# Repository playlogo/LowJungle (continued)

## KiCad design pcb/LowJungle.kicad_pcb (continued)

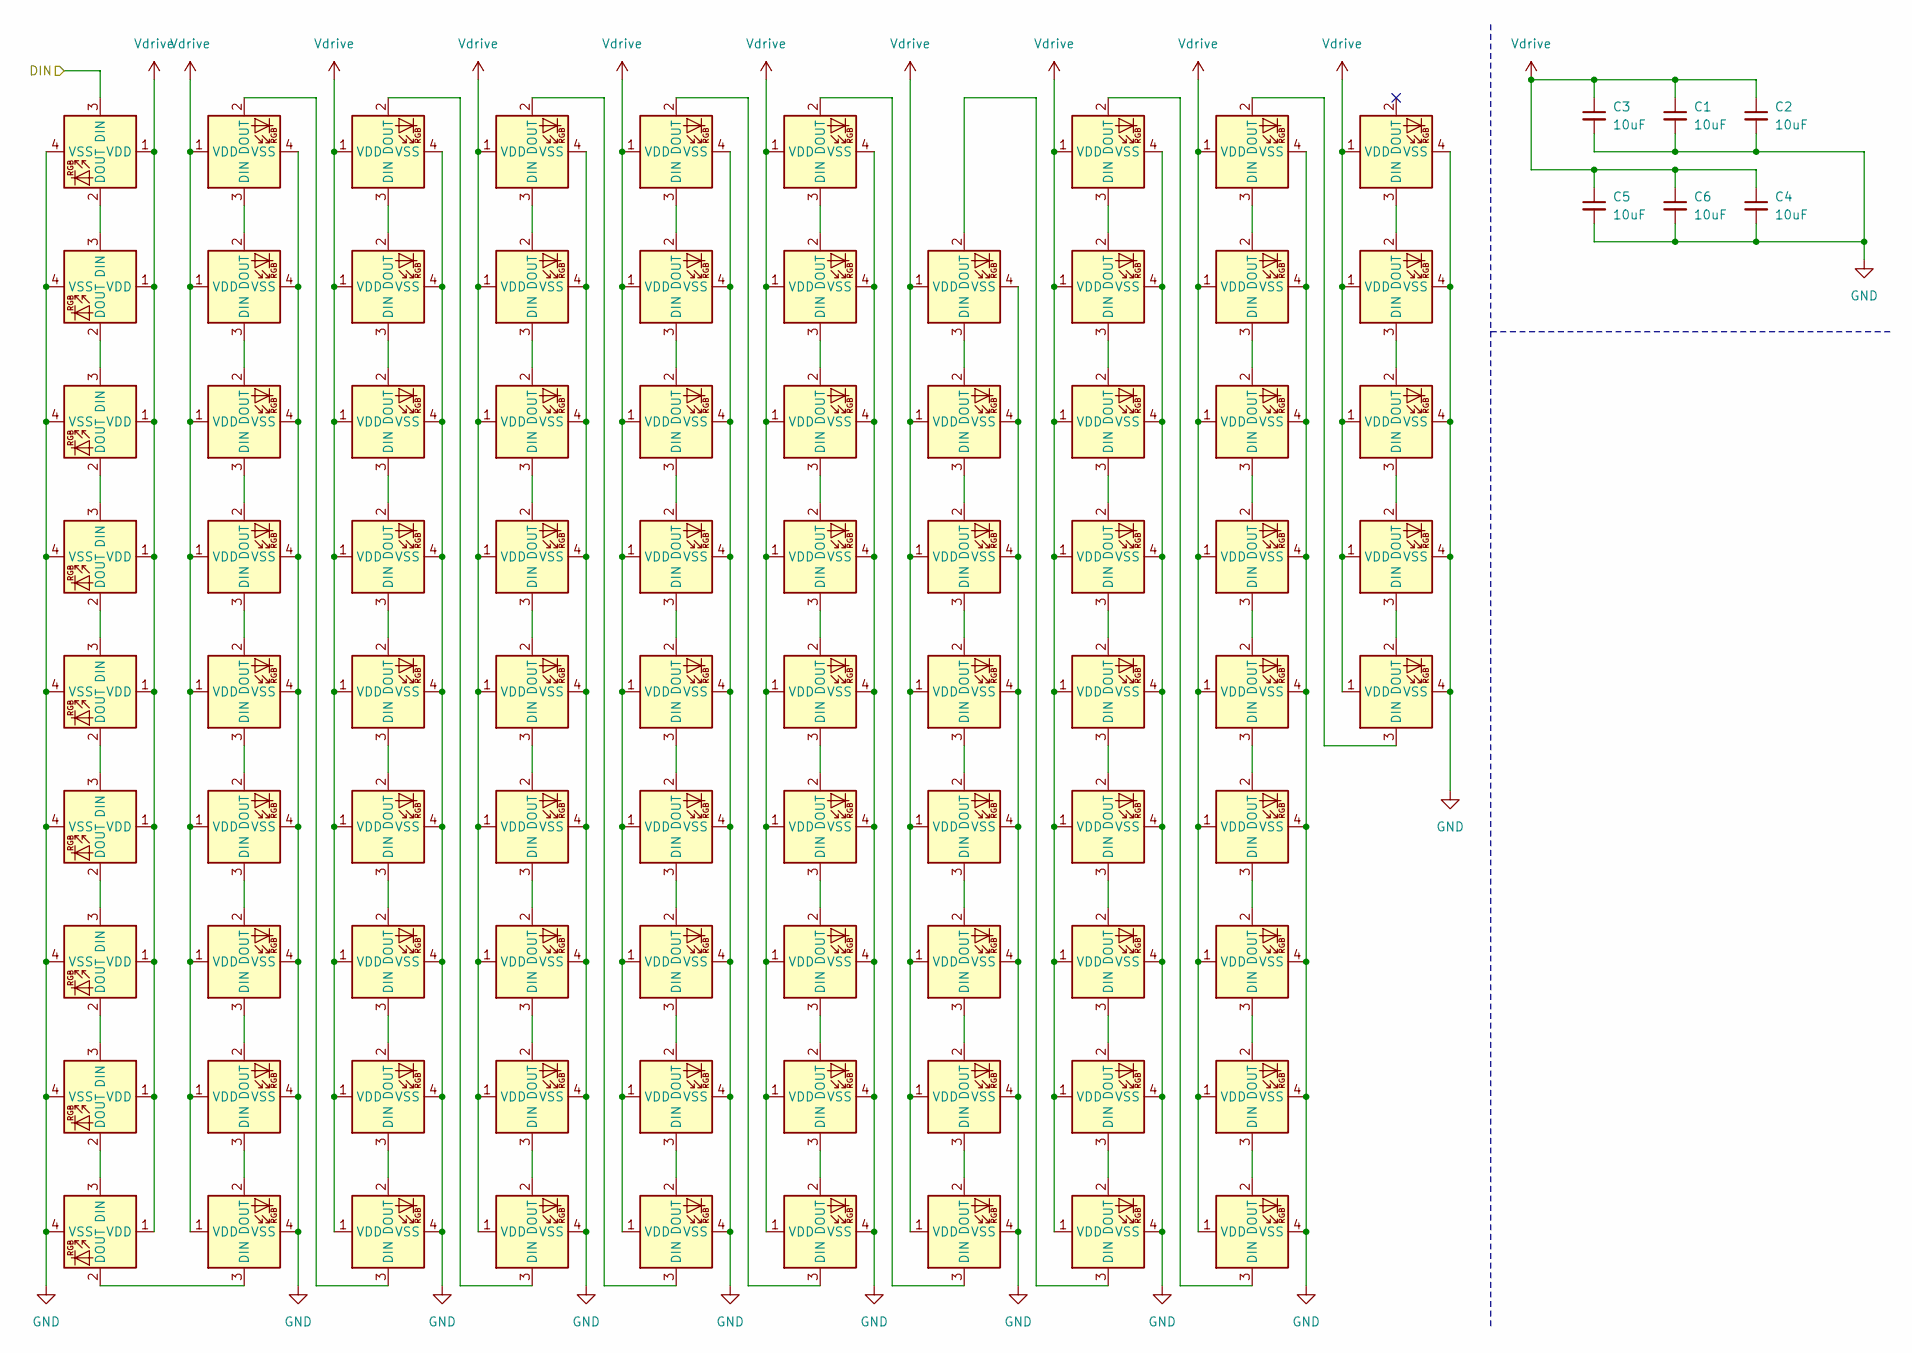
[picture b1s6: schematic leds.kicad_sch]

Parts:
C1, C2, C3, C4, C5, C6: 10uF; C_0805_2012Metric_Pad1.18x1.45mm_HandSolder
LED1, LED2, LED3, LED4, LED5, LED6, LED7, LED8, LED9, LED10, LED11, LED12, LED13, LED14, LED15, LED16, LED17, LED18, LED19, LED20, LED21, LED22, LED23, LED24, LED25, LED26, LED27, LED28, LED29, LED30, LED31, LED32, LED33, LED34, LED35, LED36, LED37, LED38, LED39, LED40, LED41, LED42, LED43, LED44, LED45, LED46, LED47, LED48, LED49, LED50, LED51, LED52, LED53, LED54, LED55, LED56, LED57, LED58, LED59, LED60, LED61, LED62, LED63, LED64, LED65, LED66, LED67, LED68, LED69, LED70, LED71, LED72, LED73, LED74, LED75, LED76, LED77, LED78, LED79, LED80, LED81, LED82, LED83, LED84, LED85: KS33_SK6812MINI-E; LED_KS33_6028R

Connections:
/LEDs/DIN: LED15.3 (DIN); also elsewhere on the board
GND: C1.2, C2.2, C3.2, C4.2, C5.2, C6.2, LED1.4 (VSS), LED2.4 (VSS), LED3.4 (VSS), LED4.4 (VSS), LED5.4 (VSS), LED6.4 (VSS), LED7.4 (VSS), LED8.4 (VSS), LED9.4 (VSS), LED10.4 (VSS), LED11.4 (VSS), LED12.4 (VSS), LED13.4 (VSS), LED14.4 (VSS), LED15.4 (VSS), LED16.4 (VSS), LED17.4 (VSS), LED18.4 (VSS), LED19.4 (VSS), LED20.4 (VSS), LED21.4 (VSS), LED22.4 (VSS), LED23.4 (VSS), LED24.4 (VSS), LED25.4 (VSS), LED26.4 (VSS), LED27.4 (VSS), LED28.4 (VSS), LED29.4 (VSS), LED30.4 (VSS), LED31.4 (VSS), LED32.4 (VSS), LED33.4 (VSS), LED34.4 (VSS), LED35.4 (VSS), LED36.4 (VSS), LED37.4 (VSS), LED38.4 (VSS), LED39.4 (VSS), LED40.4 (VSS), LED41.4 (VSS), LED42.4 (VSS), LED43.4 (VSS), LED44.4 (VSS), LED45.4 (VSS), LED46.4 (VSS), LED47.4 (VSS), LED48.4 (VSS), LED49.4 (VSS), LED50.4 (VSS), LED51.4 (VSS), LED52.4 (VSS), LED53.4 (VSS), LED54.4 (VSS), LED55.4 (VSS), LED56.4 (VSS), LED57.4 (VSS), LED58.4 (VSS), LED59.4 (VSS), LED60.4 (VSS), LED61.4 (VSS), LED62.4 (VSS), LED63.4 (VSS), LED64.4 (VSS), LED65.4 (VSS), LED66.4 (VSS), LED67.4 (VSS), LED68.4 (VSS), LED69.4 (VSS), LED70.4 (VSS), LED71.4 (VSS), LED72.4 (VSS), LED73.4 (VSS), LED74.4 (VSS), LED75.4 (VSS), LED76.4 (VSS), LED77.4 (VSS), LED78.4 (VSS), LED79.4 (VSS), LED80.4 (VSS), LED81.4 (VSS), LED82.4 (VSS), LED83.4 (VSS), LED84.4 (VSS), LED85.4 (VSS); also elsewhere on the board
unnamed: LED1.3 (DIN), LED18.2 (DOUT)
unnamed: LED1.2 (DOUT), LED2.3 (DIN)
unnamed: LED2.2 (DOUT), LED3.3 (DIN)
unnamed: LED3.2 (DOUT), LED4.3 (DIN)
unnamed: LED4.2 (DOUT), LED5.3 (DIN)
unnamed: LED5.2 (DOUT), LED6.3 (DIN)
unnamed: LED6.2 (DOUT), LED7.3 (DIN)
unnamed: LED7.2 (DOUT), LED8.3 (DIN)
unnamed: LED8.2 (DOUT), LED9.3 (DIN)
unnamed: LED10.3 (DIN), LED11.2 (DOUT)
unnamed: LED10.2 (DOUT), LED27.3 (DIN)
unnamed: LED11.3 (DIN), LED12.2 (DOUT)
unnamed: LED12.3 (DIN), LED13.2 (DOUT)
unnamed: LED13.3 (DIN), LED14.2 (DOUT)
unnamed: LED9.2 (DOUT), LED14.3 (DIN)
unnamed: LED15.2 (DOUT), LED16.3 (DIN)
unnamed: LED16.2 (DOUT), LED17.3 (DIN)
unnamed: LED17.2 (DOUT), LED18.3 (DIN)
unnamed: LED19.3 (DIN), LED20.2 (DOUT)
unnamed: LED19.2 (DOUT), LED36.3 (DIN)
unnamed: LED20.3 (DIN), LED21.2 (DOUT)
unnamed: LED21.3 (DIN), LED22.2 (DOUT)
unnamed: LED22.3 (DIN), LED23.2 (DOUT)
unnamed: LED23.3 (DIN), LED24.2 (DOUT)
unnamed: LED24.3 (DIN), LED25.2 (DOUT)
unnamed: LED25.3 (DIN), LED26.2 (DOUT)
unnamed: LED26.3 (DIN), LED27.2 (DOUT)
unnamed: LED28.3 (DIN), LED29.2 (DOUT)
unnamed: LED28.2 (DOUT), LED45.3 (DIN)
unnamed: LED29.3 (DIN), LED30.2 (DOUT)
unnamed: LED30.3 (DIN), LED31.2 (DOUT)
unnamed: LED31.3 (DIN), LED32.2 (DOUT)
unnamed: LED32.3 (DIN), LED33.2 (DOUT)
unnamed: LED33.3 (DIN), LED34.2 (DOUT)
unnamed: LED34.3 (DIN), LED35.2 (DOUT)
unnamed: LED35.3 (DIN), LED36.2 (DOUT)
unnamed: LED37.3 (DIN), LED38.2 (DOUT)
unnamed: LED37.2 (DOUT), LED54.3 (DIN)
unnamed: LED38.3 (DIN), LED39.2 (DOUT)
unnamed: LED39.3 (DIN), LED40.2 (DOUT)
unnamed: LED40.3 (DIN), LED41.2 (DOUT)
unnamed: LED41.3 (DIN), LED42.2 (DOUT)
unnamed: LED42.3 (DIN), LED43.2 (DOUT)
unnamed: LED43.3 (DIN), LED44.2 (DOUT)
unnamed: LED44.3 (DIN), LED45.2 (DOUT)
unnamed: LED46.3 (DIN), LED47.2 (DOUT)
unnamed: LED46.2 (DOUT), LED63.3 (DIN)
unnamed: LED47.3 (DIN), LED48.2 (DOUT)
unnamed: LED48.3 (DIN), LED49.2 (DOUT)
unnamed: LED49.3 (DIN), LED50.2 (DOUT)
unnamed: LED50.3 (DIN), LED51.2 (DOUT)
unnamed: LED51.3 (DIN), LED52.2 (DOUT)
unnamed: LED52.3 (DIN), LED53.2 (DOUT)
unnamed: LED53.3 (DIN), LED54.2 (DOUT)
unnamed: LED55.3 (DIN), LED82.2 (DOUT)
unnamed: LED56.3 (DIN), LED57.2 (DOUT)
unnamed: LED56.2 (DOUT), LED72.3 (DIN)
unnamed: LED57.3 (DIN), LED58.2 (DOUT)
unnamed: LED58.3 (DIN), LED59.2 (DOUT)
unnamed: LED59.3 (DIN), LED60.2 (DOUT)
unnamed: LED60.3 (DIN), LED61.2 (DOUT)
unnamed: LED61.3 (DIN), LED62.2 (DOUT)
unnamed: LED62.3 (DIN), LED63.2 (DOUT)
unnamed: LED64.3 (DIN), LED65.2 (DOUT)
unnamed: LED64.2 (DOUT), LED81.3 (DIN)
unnamed: LED65.3 (DIN), LED66.2 (DOUT)
unnamed: LED66.3 (DIN), LED67.2 (DOUT)
unnamed: LED67.3 (DIN), LED68.2 (DOUT)
unnamed: LED68.3 (DIN), LED69.2 (DOUT)
unnamed: LED69.3 (DIN), LED70.2 (DOUT)
unnamed: LED70.3 (DIN), LED71.2 (DOUT)
unnamed: LED71.3 (DIN), LED72.2 (DOUT)
unnamed: LED73.3 (DIN), LED74.2 (DOUT)
unnamed: LED73.2 (DOUT), LED85.3 (DIN)
unnamed: LED74.3 (DIN), LED75.2 (DOUT)
unnamed: LED75.3 (DIN), LED76.2 (DOUT)
unnamed: LED76.3 (DIN), LED77.2 (DOUT)
unnamed: LED77.3 (DIN), LED78.2 (DOUT)
unnamed: LED78.3 (DIN), LED79.2 (DOUT)
unnamed: LED79.3 (DIN), LED80.2 (DOUT)
unnamed: LED80.3 (DIN), LED81.2 (DOUT)
unnamed: LED82.3 (DIN), LED83.2 (DOUT)
unnamed: LED83.3 (DIN), LED84.2 (DOUT)
unnamed: LED84.3 (DIN), LED85.2 (DOUT)
Vdrive: C1.1, C2.1, C3.1, C4.1, C5.1, C6.1, LED1.1 (VDD), LED2.1 (VDD), LED3.1 (VDD), LED4.1 (VDD), LED5.1 (VDD), LED6.1 (VDD), LED7.1 (VDD), LED8.1 (VDD), LED9.1 (VDD), LED10.1 (VDD), LED11.1 (VDD), LED12.1 (VDD), LED13.1 (VDD), LED14.1 (VDD), LED15.1 (VDD), LED16.1 (VDD), LED17.1 (VDD), LED18.1 (VDD), LED19.1 (VDD), LED20.1 (VDD), LED21.1 (VDD), LED22.1 (VDD), LED23.1 (VDD), LED24.1 (VDD), LED25.1 (VDD), LED26.1 (VDD), LED27.1 (VDD), LED28.1 (VDD), LED29.1 (VDD), LED30.1 (VDD), LED31.1 (VDD), LED32.1 (VDD), LED33.1 (VDD), LED34.1 (VDD), LED35.1 (VDD), LED36.1 (VDD), LED37.1 (VDD), LED38.1 (VDD), LED39.1 (VDD), LED40.1 (VDD), LED41.1 (VDD), LED42.1 (VDD), LED43.1 (VDD), LED44.1 (VDD), LED45.1 (VDD), LED46.1 (VDD), LED47.1 (VDD), LED48.1 (VDD), LED49.1 (VDD), LED50.1 (VDD), LED51.1 (VDD), LED52.1 (VDD), LED53.1 (VDD), LED54.1 (VDD), LED55.1 (VDD), LED56.1 (VDD), LED57.1 (VDD), LED58.1 (VDD), LED59.1 (VDD), LED60.1 (VDD), LED61.1 (VDD), LED62.1 (VDD), LED63.1 (VDD), LED64.1 (VDD), LED65.1 (VDD), LED66.1 (VDD), LED67.1 (VDD), LED68.1 (VDD), LED69.1 (VDD), LED70.1 (VDD), LED71.1 (VDD), LED72.1 (VDD), LED73.1 (VDD), LED74.1 (VDD), LED75.1 (VDD), LED76.1 (VDD), LED77.1 (VDD), LED78.1 (VDD), LED79.1 (VDD), LED80.1 (VDD), LED81.1 (VDD), LED82.1 (VDD), LED83.1 (VDD), LED84.1 (VDD), LED85.1 (VDD); also elsewhere on the board

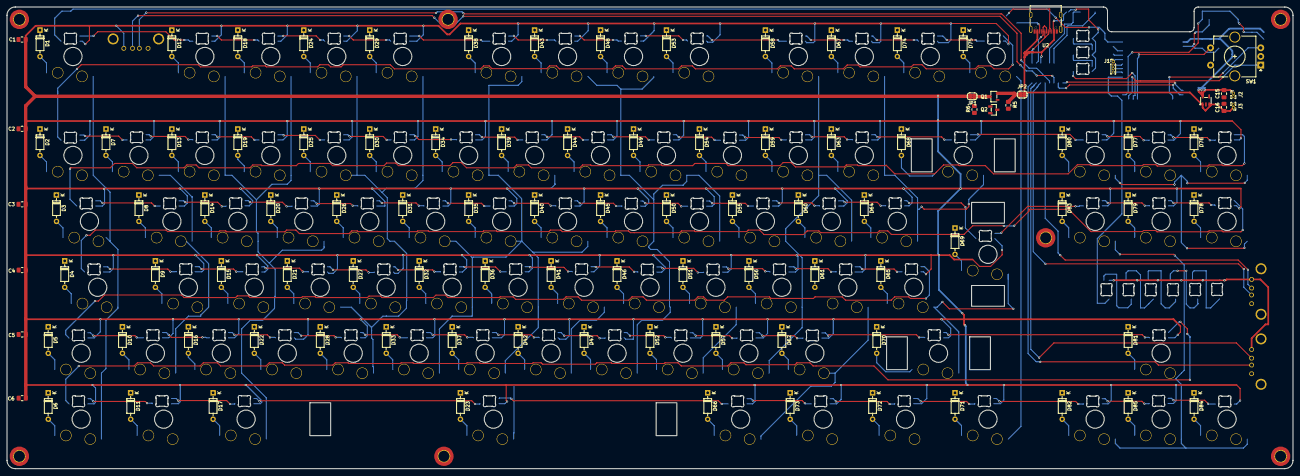
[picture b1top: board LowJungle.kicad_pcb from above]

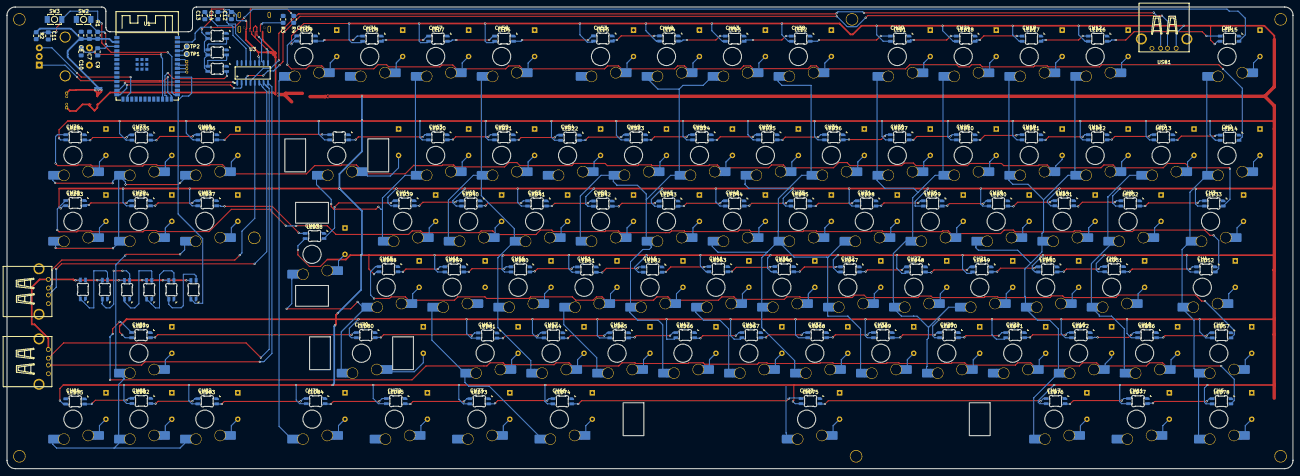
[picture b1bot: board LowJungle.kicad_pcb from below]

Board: 2 copper layers, 371.5 x 133.4 mm, 312 parts (115 on the bottom side), 231 nets.

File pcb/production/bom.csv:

Designator,Footprint,Quantity,Value,LCSC Part #
"C1, C12, C13, C14, C2, C3, C4, C5, C6, C8",0805,10,10uF,
"C10, C11, C7",0805,3,100nF,
"C15, C16, C9",0805,3,1uF,
"CH1, CH10, CH12, CH13, CH14, CH15, CH16, CH18, CH19, CH2, CH20, CH21, CH22, CH24, CH25, CH26, CH27, CH28, CH29, CH30, CH31, CH32, CH33, CH34, CH35, CH36, CH37, CH38, CH39, CH40, CH41, CH42, CH43, CH44, CH45, CH46, CH47, CH48, CH49, CH50, CH51, CH52, CH53, CH54, CH55, CH56, CH57, CH58, CH59, CH60, CH61, CH62, CH63, CH64, CH65, CH67, CH7, CH74, CH75, CH76, CH77, CH78, CH79, CH8, CH80, CH81, CH82, CH83, CH84, CH85, CH9",SW_KS33_HS_KS-2P02B01-02_1u,71,KS33_SW_HS,
"CH11, CH17, CH5, CH6, CH66, CH71, CH72, CH73",SW_KS33_HS_KS-2P02B01-02_1.25u,8,KS33_SW_HS,
CH23,SW_KS33_HS_KS-2P02B01-02_6.25,1,KS33_SW_HS,
CH3,SW_KS33_HS_KS-2P02B01-02_1.5u,1,KS33_SW_HS,
CH4,SW_KS33_HS_KS-2P02B01-02_1.75u,1,KS33_SW_HS,
CH68,SW_KS33_HS_KS-2P02B01-02_2u,1,KS33_SW_HS,
CH69,SW_KS33_HS_KS-2P02B01-02_Enter,1,KS33_SW_HS,
CH70,SW_KS33_HS_KS-2P02B01-02_2.75u,1,KS33_SW_HS,
"D1, D10, D11, D12, D13, D14, D15, D16, D17, D18, D19, D2, D20, D21, D22, D23, D24, D25, D26, D27, D28, D29, D3, D30, D31, D32, D33, D34, D35, D36, D37, D38, D39, D4, D40, D41, D42, D43, D44, D45, D46, D47, D48, D49, D5, D50, D51, D52, D53, D54, D55, D56, D57, D58, D59, D6, D60, D61, D62, D63, D64, D65, D66, D67, D68, D69, D7, D70, D71, D72, D73, D74, D75, D76, D77, D78, D79, D8, D80, D81, D82, D83, D84, D85, D9",D_DO-35_SOD27_P7.62mm_Horizontal,85,D_Small,
J1,PinHeader_1x04_P1.00mm_Vertical,1,JTAG,
J2,PinHeader_1x02_P1.00mm_Vertical,1,3.3V,
J3,PinHeader_1x02_P1.00mm_Vertical,1,5V,
LDO1,SOT-23-5_L3.0-W1.7-P0.95-LS2.8-BL,1,ME6211C33M5G-N,C82942
"LED1, LED10, LED11, LED12, LED13, LED14, LED15, LED16, LED17, LED18, LED19, LED2, LED20, LED21, LED22, LED23, LED24, LED25, LED26, LED27, LED28, LED29, LED3, LED30, LED31, LED32, LED33, LED34, LED35, LED36, LED37, LED38, LED39, LED4, LED40, LED41, LED42, LED43, LED44, LED45, LED46, LED47, LED48, LED49, LED5, LED50, LED51, LED52, LED53, LED54, LED55, LED56, LED57, LED58, LED59, LED6, LED60, LED61, LED62, LED63, LED64, LED65, LED66, LED67, LED68, LED69, LED7, LED70, LED71, LED72, LED73, LED74, LED75, LED76, LED77, LED78, LED79, LED8, LED80, LED81, LED82, LED83, LED84, LED85, LED86, LED87, LED88, LED89, LED9, LED90, LED91, LED92, LED93, LED94",LED_KS33_6028R,94,KS33_SK6812MINI-E,
Q1,SOT-23-3_L3.0-W1.7-P0.95-LS2.9-BR,1,CJ2301 S1,C8547
Q2,SOT-23-3_L2.9-W1.3-P1.90-LS2.4-BR,1,SI2302_C2891732,C2891732
"R1, R2, R5",0805,3,10k,
"R3, R4, R6",0805,3,5.1k,
SW1,RotaryEncoder_Alps_EC11E-Switch_Vertical_H20mm_CircularMountingHoles,1,RotaryEncoder_Switch,
"SW2, SW3",SW-SMD_L3.9-W2.9-LS5.0,2,GT-TC029A-H020-L1N,C778164
TP1,TestPoint_Pad_D1.0mm,1,RX,
TP2,TestPoint_Pad_D1.0mm,1,TX,
U1,WIRELM-SMD_ESP32-S3-WROOM-1,1,ESP32-S3-WROOM-1(N8R2),C2913204
U2,USB-C-SMD_G-SWITCH_GT-USB-7010ASV,1,GT-USB-7010ASV,C2988369
U3,SOP-16_L10.0-W3.9-P1.27-LS6.0-BL,1,SL2.1A,C192893
"USB1, USB2",USB-A-TH_USB-A-F-90,2,KH-AF90DIP-112,C503996
USB3,USB-A-TH_USB-A-F-90,1,DNP,C503996

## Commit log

2025-03-14 update gitignore
2025-03-14 Created keymatrix
2025-03-15 Move all hot swap socket to flipping right side
2025-03-15 Routing
2025-03-15 ledsssssss
2025-03-15 Added stabilizers
2025-03-15 Finished schematic
2025-03-15 Started routing
2025-03-15 Finished PCB!!
2025-03-16 Finished PCB, added BOM, improved docs
2025-03-16 improved formatting
2025-03-16 added more mounting holes
2025-03-16 Moved usb-c plug to other side
2025-03-16 Improved silkscreen, added foam to bom
2025-03-16 Added case
2025-03-16 push
2025-03-18 Improved case! Added fasteners section to documentation
2025-05-09 Create LICENSE
